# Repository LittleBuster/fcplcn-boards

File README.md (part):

# FCPLCn — платы контроллера

**Future City PLC Next · FCPLCN-161608-1v0**

**16 реле · 16 дискретных входов · 8 DATA-линий · Ethernet · Wi-Fi · RS-485 · iButton LED/звук**

Двухплатный PLC для локальной автоматики квартиры, частного дома и дачи.
Верхняя плата содержит процессор, сетевые интерфейсы, часы и полевые порты.
Нижняя — реле, входы, расширители GPIO, энергонезависимую FRAM и вход питания.
Прошивка выполняет местную логику управления, а Linux-хаб объединяет несколько PLC
в общий умный дом.

<p align="center">
  <a href="#overview">Характеристики</a> ·
  <a href="#cpu">CPU-плата</a> ·
  <a href="#relay">Реле и входы</a> ·
  <a href="#ports">Разъёмы и GPIO</a> ·
  <a href="#ibutton">iButton-панель</a> ·
  <a href="#power">Питание</a> ·
  <a href="#schematics">Схемы</a> ·
  <a href="#files">Файлы проекта</a>
</p>

Рендеры показывают конструкцию комплекта. Характеристики ниже сверены с текущими
схемами, нетлистами и BOM; токи обозначены как расчётные бюджеты.
Подробная аппаратная квалификация образца остаётся отдельным этапом.

Для тестового устройства предыдущего поколения **FCPLC-080806-3v1** также добавлены
[исправленная PDF-схема и сведения о подключении EEPROM](FCPLC-080806-3v1/README.md).
Его профиль в прошивке использует 8 реле, 8 входов и EEPROM 24LC512 вместо FRAM.

## Комплект FCPLCN-161608-1v0

| Узел              | Исполнение                                                               |
| ----------------- | ------------------------------------------------------------------------ |
| Верхняя плата     | **FCPLCN-CPU-08-1v0**, 90,5 × 49,44 мм                                     |
| Нижняя плата      | **FCPLCN-RLY-1616-1v0**, 101 × 86 мм                                     |
| Процессор         | ESP32-S3-WROOM-1U-N16R8, внешняя антенна 2,4 ГГц                         |
| Память процессора | 16 МиБ Flash и 8 МиБ PSRAM                                               |
| Релейные выходы   | 16 независимых нормально разомкнутых пар **COM/NO**                      |
| Дискретные входы  | 16 входов для сухого контакта с TLP2363 и RC-фильтрами                   |
| DATA              | 8 линий через ISO1640 для интерфейсов с открытым стоком                  |
| Сеть              | Wi-Fi ESP32-S3 и Ethernet на W5500-Lite / USR-ES1                        |
| RS-485            | ADM2687EBRIZ, полудуплекс, управление направлением через GPIO            |
| iButton-панель    | J9: LED− / BZ− через ULN2001 и общий защищённый +12V                    |
| Часы              | DS3231MZ+, резервирование от **CR1220 3 В**                              |
| FRAM              | FM24CL64B-GTR, **8192 байта**, на нижней плате                           |
| Питание комплекта | Внешние **12 В DC**, ввод на нижней плате                                |
| Технология PCB    | Обе платы двухслойные, толщина 1,6 мм                                    |
| Спецификация      | CPU **164** + RLY **248** = **412** покупных деталей; батарейка отдельно |

Числа `16 / 16 / 08` в обозначении комплекта соответствуют реле, дискретным входам
и DATA-линиям. Это одна аппаратная конфигурация с двумя физическими платами.

### Как связаны платы

Внутренняя I²C соединяет ESP32-S3, два MCP23017, FRAM и RTC. Отдельная линия
сбрасывает расширители GPIO. Межплатные разъёмы передают защищённые 12 В и GND; местные 5 В и 3,3 В между платами не передаются.
Внешние DATA, I²C и RS-485 отделены от основной логики барьером, но используют
**общую `GND_ISO`**. Дискретные входы относятся к основной GND.

## Верхняя плата — FCPLCN-CPU-08-1v0

CPU-плата отвечает за автономную логику PLC, подключение к локальной сети,
чтение полевых датчиков и сервисный USB. ESP32-S3 установлен в исполнении
с разъёмом внешней антенны. W5500 подключён по SPI; разъём RJ45 расположен
у переднего края сборки.

На обратной стороне находятся RTC, держатель батарейки и часть обвязки:

| Обозначение  | Компонент                | Назначение                                     |
| ------------ | ------------------------ | ---------------------------------------------- |
| U1           | ESP32-S3-WROOM-1U-N16R8  | Контроллер, Wi-Fi, Flash и PSRAM               |
| U2           | W5500-Lite / USR-ES1     | Проводной Ethernet по SPI                      |
| U3           | R-78K3.3-1.0             | Основное питание CPU 3,3 В                     |
| U4           | TMR-1-0511               | Изолированное питание 5 В, всего 1 Вт          |
| U5           | R-78K3.3-0.5             | Полевое питание `3V3_ISO`                      |
| U6/U8/U9/U15 | ISO1640BDR               | Восемь DATA-линий, по две на микросхему        |
| U7           | ISO1640BDR               | Внешняя I²C на J5                              |
| U10 / BT1    | DS3231MZ+ / Q&J CR1220-2 | Часы и резервная батарейка                     |
| U11          | ADM2687EBRIZ             | Изолированный трансивер RS-485                 |
| U12          | R-78K3.3-0.5             | Отдельное основное питание RS-485 3,3 В        |
| U13/U14      | Nexperia 74LVC125AD,118  | Буферы сигналов между основными цепями питания |
| U16          | ULN2001D1013TR          | Управляемые минусы LED и буззера iButton-панели |
| U17          | R-78E5.0-1.0            | Местные 5 В для входа TMR, от защищённых 12 В |

### DATA и внешняя I²C

J3 выводит восемь DATA-линий, питание `5V_ISO` и `GND_ISO`. Это линии
с открытым стоком: в аппаратном профиле они соответствуют `sens-0/1`…`sens-0/8`.
Они предусмотрены для трёхпроводных OneWire/DHT22-подключений с отдельным питанием.
Полевые подтяжки DATA подключены к **5 В**.

J5 — отдельная внешняя I²C: `3V3_ISO`, SDA, SCL, `GND_ISO`.
Её сигналы подтянуты к **3,3 В**. Она использует другую пару GPIO, чем внутренняя
шина расширителей и памяти. Устройства на J5 не занимают адреса внутренней I²C.

### RS-485

J8 содержит `5V_ISO`, A/D+, B/D− и `GND_ISO`. GPIO48 управляет направлением:
HIGH — передача, LOW — приём. Терминатор **120 Ом** включается перемычкой JP2,
расположенной спереди между J3 и J8 рядом с надписью `120R`.

Питание 5 В на J8 поступает от общего полевого TMR. Внутренний источник isoPower
ADM2687E обслуживает сам трансивер и не является источником питания DATA/I²C.
Конкретный протокол RS-485 задаётся программным обеспечением; наличие трансивера
не означает автоматическую поддержку любого протокола.

### Индикация и звук iButton-панели

**J9 — трёхконтактный KF128-2.54-3P** на нижнем переднем краю CPU-платы,
между Ethernet и DATA. Ввод проводов направлен наружу. На рендере сверху
контакты идут слева направо:

| Контакт J9 | Надпись на плате | Подключение панели | Управление |
| ---------- | ---------------- | ------------------ | ---------- |
| 1 | **LED−** | Катод светодиода | GPIO43, HIGH — включён |
| 2 | **BZ−** | Минус буззера | GPIO45, HIGH — включён |
| 3 | **+12V** | Анод LED и плюс буззера | Общая защищённая ветка питания |

Выходы LED− и BZ− замыкают нагрузку на основную GND через
**ULN2001D1013TR, SOIC-16, шаг 1,27 мм**. Драйвер U16 и основная обвязка
расположены на обратной стороне CPU-платы под W5500.

Для голого светодиода на плате предусмотрен R75 **1 кОм / 0,5 Вт, 0805**:
анод LED подключается к +12V, катод — к LED−. Ожидаемый ток около 6–8 мА.
Буззер подключается плюсом к +12V, минусом к BZ−; расчётная нагрузка —
до 100 мА. Для активного буззера достаточно ON/OFF, пассивный требует частотного
сигнала в прошивке. Точный тип и рабочее напряжение проверяются на реальном буззере.

Питание панели проходит через PTC, SS14 и местные 22 мкФ + 100 нФ;
SMAJ15A ограничивает выбросы, COM драйвера подключён к этой же ветке.
«12V» означает номинальную 12-вольтовую систему: при полной расчётной нагрузке
с учётом потерь на фильтре, диоде, PTC и ULN на буззере возможно около 8,5–9 В.

GPIO43 подтянут к основной GND через R73 10 кОм. R74 10 кОм подключён к базе
буззера; GPIO45 подтянут через R72 + R74, всего 10,68 кОм, когда вывод высокоимпедансный.
GPIO45 является загрузочным: LOW сохраняет 3,3 В VDD_SPI при штатных eFuse ESP32-S3.
GPIO43 может активно управляться ROM UART0 TX до настройки приложением; подтяжка
не подавляет этот сигнал, поэтому LED может мигать или гореть при загрузке.
Для постоянных логов предусмотрена USB-консоль.

**Сам сокет ключа iButton подключается отдельно к выбранной линии DATA на J3
и GND_ISO.** J9 обслуживает только свет и звук; отдельного GND на нём нет.
Контакты сокета не следует соединять с цепями LED/буззера и основной GND внутри панели.

### RTC и USB

DS3231MZ+ находится на внутренней I²C по адресу **`0x68`**. Батарейка —
**CR1220 3 В**, держатель Q&J CR1220-2, LCSC C70381; покупается отдельно.
FRAM имеет самостоятельное энергонезависимое хранение и батарейки не требует.

USB-C J2 используется для штатного USB Serial/JTAG ESP32-S3. D−/D+ подключены
к GPIO19/20, VBUS контролируется через GPIO21. **Для работы и прошивки через USB
нужно штатное питание 12 В:** USB VBUS служит сигналом контроля и не питает платы.
На плате доступны кнопки RESET и BOOT.

## Нижняя плата — FCPLCN-RLY-1616-1v0

Нижняя плата объединяет шестнадцать реле, шестнадцать дискретных входов,
два MCP23017, FRAM и питание всего комплекта. Верхний ряд клемм — выходные
контакты реле, нижний — входы DI с соседними GND; справа расположен ввод 12 В.

### Реле

K1…K16 — **HF49FD/012-1H11** с катушками 12 В. Каждый канал имеет свою пару
COM/NO на отдельном клеммнике J2…J17. Силовые COM разных каналов внутри платы
не объединены. U3/U4 **TBD62083AFWG** управляют катушками, а RN1/RN2 задают
подтяжки управляющих линий к GND.

```text
Реле выключено:  COM  o     o  NO
Реле включено:   COM  o─────o  NO

MCP23017 → TBD62083AFWG → катушка K1…K16
```

При сборке допустимая нагрузка определяется всем трактом: контактами выбранного
реле, дорожками, клеммами и проводкой. Число каналов не задаёт допустимый ток
силовой части.

### Дискретные входы

J21/J25/J29/J33 принимают четыре группы по четыре сухих контакта.
У каждого DI рядом расположен GND. Состояния на стороне MCP23017:

| Контакт между DI и GND | Уровень входа |
| ---------------------- | ------------- |
| Разомкнут              | **HIGH**      |
| Замкнут                | **LOW**       |

Каждый канал содержит TLP2363, входной TVS, обратный диод и две ступени фильтрации.
В текущей ревизии входная цепь использует **1,2 кОм**, последовательные **220 Ом**,
ёмкость **1 мкФ** и шунт LED **4,7 кОм**. На выходе остаются **470 Ом / 100 нФ**
и внешняя подтяжка RAW-сигнала **10 кОм**. Внутренние подтяжки MCP23017 отключены.

Цепь LED питается от внутренних 12 В. DI рассчитан на замыкание сухим контактом;
его нельзя трактовать как свободный GPIO 3,3 В. **Земля DI общая с логикой**:
TLP2363 здесь не образуют отдельный гальванически изолированный домен входов.
Примеры назначений — возвратная кнопка, геркон или релейный выход датчика.

### Расширители и FRAM

U5/U6 **MCP23017** обслуживают по восемь реле и восемь входов.
Обозначения портов MCP повторяются на каждой микросхеме:

| Номер в группе | Реле      | Дискретный вход |
| -------------- | --------- | --------------- |
| 1…7            | GPA1…GPA7 | GPB0…GPB6       |
| 8              | GPB7      | GPA0            |

U5 соответствует каналам **1…8**, U6 — **9…16**. Маска выходов — `0x80FE`,
входов — `0x7F01`. Аппаратный RESET расширителей приходит с CPU GPIO6;
INTA/INTB не подключены.

U9 **FM24CL64B-GTR** хранит 8192 байта без питания. A0/A1/A2 подключены к GND,
поэтому адрес — `0x50`; WP также на GND, запись разрешена. Память подключена
к той же внутренней шине, что расширители и RTC. В прошивке она используется
для сохранения оперативных состояний оборудования.

| Внутренняя I²C · GPIO4/5 | Адрес, 7 бит | Размещение                |
| ------------------------ | ------------ | ------------------------- |
| MCP23017 U5              | `0x20`       | Нижняя плата, каналы 1…8  |
| MCP23017 U6              | `0x21`       | Нижняя плата, каналы 9…16 |
| FRAM FM24CL64B-GTR U9    | `0x50`       | Нижняя плата              |
| RTC DS3231MZ+ U10        | `0x68`       | Верхняя плата             |

## Разъёмы и аппаратные имена

**Нумерация ниже — номера контактов в KiCad**, а не направление слева направо
на произвольно повёрнутом рендере. Первый контакт сверяется по исходнику и
маркировке конкретного разъёма.

| Плата / разъём | Назначение         | Контакты по номерам                                     |
| -------------- | ------------------ | ------------------------------------------------------- |
| RLY · J1       | Питание комплекта  | 1 — +12 В DC; 2 — GND                                   |
| RLY · J2…J17   | Реле 1…16          | 1 — COM; 2 — NO                                         |
| RLY · J21      | Входы 1…4          | Нечётные 1/3/5/7 — DI1/2/3/4; чётные — GND              |
| RLY · J25      | Входы 5…8          | Нечётные 1/3/5/7 — DI5/6/7/8; чётные — GND              |
| RLY · J29      | Входы 9…12         | Нечётные 1/3/5/7 — DI9/10/11/12; чётные — GND           |
| RLY · J33      | Входы 13…16        | Нечётные 1/3/5/7 — DI13/14/15/16; чётные — GND          |
| CPU · J3       | DATA, 10 контактов | 1…8 — DATA1…8; 9 — 5V_ISO; 10 — GND_ISO                 |
| CPU · J5       | Внешняя I²C        | 1 — 3V3_ISO; 2 — SDA_ISO; 3 — SCL_ISO; 4 — GND_ISO      |
| CPU · J8       | RS-485             | 1 — 5V_ISO; 2 — A/D+; 3 — B/D−; 4 — GND_ISO             |
| CPU · J9       | iButton LED / звук | 1 — LED−; 2 — BZ− (BUZZER−); 3 — +12V панели             |
| CPU · J7       | Передняя индикация | 1 — NET; 2 — PWR; 3 — STATUS; 4 — ALARM; 5 — GND        |
| CPU · J2       | Сервисный USB-C    | USB D−/D+, VBUS sense; внешнее питание 12 В сохраняется |

### Две штатные межплатные пары

Нижние гнёзда — Samtec **SSW-103-01-L-D**, верхние гребёнки —
**TSW-103-07-L-D**. У каждой пары шесть контактов, всего между платами их двенадцать.

| Контакт | Нижний J43 ↔ верхний J1 | Нижний J44 ↔ верхний J6 |
| ------- | ----------------------- | ----------------------- |
| 1       | GND                     | GND                     |
| 2       | GND                     | GND                     |
| 3       | GND                     | +12V_LOGIC              |
| 4       | GND                     | +12V_LOGIC              |
| 5       | I2C_SDA, GPIO4          | MCP_RESET_N, GPIO6      |
| 6       | I2C_SCL, GPIO5          | GND                     |

Обозначения J1 и J6 здесь относятся к CPU; RLY J1 — отдельный ввод питания.
В текущей CAD-ревизии дополнительных механических пар разъёмов нет.

### GPIO ESP32-S3

| Назначение                   | GPIO                             |
| ---------------------------- | -------------------------------- |
| Внутренняя I²C SDA / SCL     | **4 / 5**                        |
| RESET MCP23017               | **6**                            |
| W5500 CS / SCK / MOSI / MISO | **9 / 10 / 11 / 12**             |
| W5500 INT_N / RESET_N        | **13 / 14**                      |
| USB D− / D+ / VBUS sense     | **19 / 20 / 21**                 |
| RS-485 TX / RX / DIR         | **8 / 47 / 48**                  |
| Внешняя I²C SDA / SCL        | **41 / 42**                      |
| DATA1…DATA8                  | **39, 40, 17, 18, 1, 2, 38, 44** |
| NET / STATUS / ALARM         | **7 / 15 / 16**, активный LOW    |
| iButton LED / BUZZER         | **43 / 45**, HIGH включает нагрузку |
| BOOT                         | **0**                            |

PWR показывает основное питание 3,3 В. GPIO35–37 оставлены неподключёнными
для варианта N16R8 с Octal PSRAM. GPIO44 уже используется DATA8. GPIO43/45 заняты панелью; на них установлены внешние подтяжки к GND. GPIO3 оставлен NC.

В профиле прошивки каналы имеют имена `rly-0/1`…`rly-0/16`,
`in-0/1`…`in-0/16` и `sens-0/1`…`sens-0/8`.
[Профиль аппаратуры в fcplcn-soft](https://github.com/LittleBuster/fcplcn-soft/blob/main/firmware/base/main/hardware/board_profile.cpp).

## Питание и домены земли

[Открыть схему питания SVG](docs/readme/power-domains.svg).
Ниже **CPU** означает верхнюю плату, **RLY** — нижнюю; одинаковые номера
компонентов на разных платах обозначают разные детали.

### Ввод 12 В и ветка логики

Питание приходит на **RLY J1**: `+12V / GND`. Последовательные
**F1 Littelfuse 045201.5MRL, 1,5 А** и **D1 SS34** ведут к `+12V_SYS`.
D1 блокирует обратную полярность в этой ветке; **D2 SMBJ15A** подключён
между `+12V_SYS` и GND для ограничения кратковременных выбросов.
C1/C11/C12 образуют накопительный банк **300 мкФ / 35 В**.

От `+12V_SYS` питаются **катушки 16 реле** и **светодиодные входные цепи
TLP2363**. Сухие COM/NO контакты реле электрически отделены от катушек:
напряжение коммутируемой нагрузки подаётся на них извне.

Ветка электроники идёт отдельно:
`+12V_SYS → D3 B340B → +12V_LOGIC_RAW → R12 1 Ом → +12V_LOGIC`.
**C8 220 мкФ / 35 В** и **C13 100 нФ** подключены после R12.
D3 отделяет накопленную энергию этой ветки от катушек, а R12/C8/C13
образуют фильтр питания логики. Из-за падений на диодах и R12
`+12V_LOGIC` ниже напряжения внешнего блока питания.

### Четыре местных преобразователя

Все четыре получают `+12V_LOGIC` и работают относительно основной **GND**.
Модули **R-78 — импульсные стабилизаторы без гальванической изоляции**.

| Плата и источник | Выход и его потребители | Номинал модуля | Выделенный расчётный ток |
| --- | --- | --- | --- |
| **RLY U2, R-78K3.3-0.5** | `+3V3_DCDC → FB1 → +3V3`: MCP23017, FRAM, выходные стороны TLP2363 и их обвязка | **3,3 В / 500 мА** | **100 мА**; компонентная оценка **82,9 мА** |
| **CPU U3, R-78K3.3-1.0** | Основные `+3V3`: ESP32-S3, W5500, RTC, основные стороны ISO1640, индикация и обвязка | **3,3 В / 1 А** | **902 мА** |
| **CPU U12, R-78K3.3-0.5** | `+3V3_RS485`: основная сторона ADM2687E, локальный буфер и подтяжки | **3,3 В / 500 мА** | **201 мА** |
| **CPU U17, R-78E5.0-1.0** | Местные `+5V_TMR`: только вход изолированного TMR U4 | **5 В / 1 А** | **300 мА** |

Нижний **FB1 — Murata BLM21PG221SN1D**, ферритовый фильтр с малым
сопротивлением постоянному току. C3/C6 находятся до него, C7 и местные
100 нФ микросхем — после. Нижнего линейного стабилизатора U8 больше нет.
Обе платы имеют собственные 3,3 В; **их выходы между собой не соединены**.

Между платами питание передаётся только как **`+12V_LOGIC` и GND**:
справа J44/J6 контакты **3/4 — +12V_LOGIC**, **1/2/6 — GND**, **5 — RESET MCP**.
Слева J43/J1 контакты **1–4 — GND**, **5/6 — SDA/SCL**.
Местные 5 В и 3,3 В через межплатные разъёмы не проходят.

### Питание датчиков и полевой стороны

На CPU цепочка начинается с **U17**:
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
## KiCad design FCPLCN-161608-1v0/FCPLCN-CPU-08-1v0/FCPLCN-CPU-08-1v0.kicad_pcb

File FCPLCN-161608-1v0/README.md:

# FCPLCN-161608-1v0

**FCPLCn — Future City PLC Next.** Двухплатный комплект:
16 реле, 16 дискретных входов, 8 DATA-линий и выходы LED/буззера iButton-панели.

Подробное актуальное описание, питание, GPIO и распиновки:
**[основной README репозитория](../README.md)**.

## Платы и исходники

| Плата                      | Проект KiCad                                                | Принципиальная схема                                       | Читаемый PDF                                  |
| -------------------------- | ----------------------------------------------------------- | ---------------------------------------------------------- | --------------------------------------------- |
| Верхняя CPU, 90,5 × 49,44 мм | [Проект](FCPLCN-CPU-08-1v0/FCPLCN-CPU-08-1v0.kicad_pro)     | [KiCad](FCPLCN-CPU-08-1v0/FCPLCN-CPU-08-1v0.kicad_sch)     | [PDF](FCPLCN-CPU-08-1v0/FCPLCN-CPU-08-1v0-schematic.pdf)   |
| Нижняя RLY, 101 × 86 мм    | [Проект](FCPLCN-RLY-1616-1v0/FCPLCN-RLY-1616-1v0.kicad_pro) | [KiCad](FCPLCN-RLY-1616-1v0/FCPLCN-RLY-1616-1v0.kicad_sch) | [PDF](FCPLCN-RLY-1616-1v0/FCPLCN-RLY-1616-1v0-schematic.pdf) |

CPU содержит ESP32-S3-WROOM-1U-N16R8, W5500-Lite, RTC DS3231MZ+,
полевые DATA/I²C и трансивер RS-485 ADM2687E. На нижней плате расположены
реле HF49FD/012-1H11, входные TLP2363 с RC-фильтрами, два MCP23017
и FRAM FM24CL64B-GTR на 8192 байта.

Текущая комплектация: **CPU 164 + RLY 248 = 412** покупных деталей;
батарейка **CR1220 3 В** покупается отдельно. Обе платы двухслойные, 1,6 мм.
Две штатные пары межплатных разъёмов передают питание, I²C и RESET MCP.
Дополнительные механические пары удалены из текущих исходников.

## Питание двух плат

**12 В DC** подаются на нижний **J1**. После предохранителя **F1 1,5 А**
и диода **D1 SS34** получается `+12V_SYS`; **D2 SMBJ15A** ограничивает
кратковременные выбросы, C1/C11/C12 образуют банк 300 мкФ / 35 В.
Эта ветка питает катушки реле и светодиодные входные цепи TLP2363.
Сухие COM/NO контакты коммутируют внешнюю нагрузку, собственных 12 В на них нет.

Ветка электроники отделена фильтром:
`+12V_SYS → D3 B340B → R12 1 Ом → +12V_LOGIC`,
с C8 220 мкФ и C13 100 нФ после R12. Защищённые `+12V_LOGIC`
питают четыре местных импульсных преобразователя без гальванической изоляции:

| Плата и модуль | Питает | Номинал выхода | Выделено по расчёту |
| --- | --- | --- | --- |
| **RLY U2 R-78K3.3-0.5** | Через **FB1 BLM21PG221SN1D** — местные 3,3 В MCP23017, FRAM и выходных сторон TLP2363 | **3,3 В / 500 мА** | **100 мА**, компонентная оценка **82,9 мА** |
| **CPU U3 R-78K3.3-1.0** | ESP32-S3, W5500, RTC, основные стороны изоляторов и обвязка | **3,3 В / 1 А** | **902 мА** |
| **CPU U12 R-78K3.3-0.5** | Основная сторона ADM2687E, буфер и подтяжки | **3,3 В / 500 мА** | **201 мА** |
| **CPU U17 R-78E5.0-1.0** | Только вход TMR U4, местная `+5V_TMR` | **5 В / 1 А** | **300 мА** |

На RLY C3/C6 находятся до FB1, C7 и местные 100 нФ — после него;
нижний линейник U8 удалён. Питание между платами передаётся только как **12 В и GND**:
правый J44/J6 — питание и RESET, левый J43/J1 — I²C и GND.
Контакты 1–4 левой пары — GND. Шины **5 В и 3,3 В между платами не передаются**.

На CPU `+5V_TMR → U4 TMR-1-0511 → +5V_ISO / GND_ISO` —
изолированное питание поля **5 В / 200 мА, всего 1 Вт**.
Оно поступает на **J3.9 DATA**, **J8.1 RS-485** и полевые стороны DATA-изоляторов.
От этой же шины **U5 R-78K3.3-0.5** формирует `+3V3_ISO` для **J5.1 I²C**
и полевой стороны её изолятора. U5 имеет номинал 500 мА, но доступная мощность
ограничена общим TMR. На собственную полевую электронику выделено 55 мА
в эквиваленте 5 В, на все внешние устройства — **120 мА суммарно**;
общий бюджет поля — 175 из 200 мА. Это общий лимит DATA/I²C/RS-485,
а не отдельный лимит каждого разъёма.

Встроенный **isoPower ADM2687E** отдельно питает только шинную сторону
самого трансивера: `VISOOUT10 → CPU FB1 → VISOIN15`.
Он не соединён с `+3V3_ISO`; питание на J8 приходит от TMR.
DATA, внешняя I²C и шинная сторона RS-485 имеют общую **GND_ISO**,
без изоляции портов друг от друга. Основная **GND** объединяет CPU и RLY.

LED/буззер панели питаются от `+12V_LOGIC` через **CPU F2 PTC и D11 SS14**
на `+12V_PANEL / J9`; ULN2001 управляет их минусами относительно основной GND.
Бюджет панели — **108 мА**. CR1220 резервирует только RTC; зарядной цепи нет.
**USB VBUS используется только для контроля на GPIO21** и не питает платы:
для работы и прошивки через USB нужны внешние **12 В**.

Все токи — расчётные бюджеты, не измеренные максимумы. Для входа TMR при 1 Вт
и типовом КПД 76% получается 263,158 мА; выделено 300 мА.
Модель всего комплекта даёт около **0,995–1,012 А от 12 В**.
Подробности и допущения — [основное описание питания](../README.md#power),
[бюджет](Power-budget.json) и [расчёт](Power-split-design-review.json).

## CPU сверху и подключение iButton-панели

Клеммник **J9, KF128-2.54-3P**, находится на нижнем переднем краю CPU-платы
между Ethernet и DATA. На виде сверху контакты идут слева направо:

| Контакт | Надпись | Подключение |
| ------- | ------- | ----------- |
| 1 | **LED−** | Катод LED; GPIO43 через ULN2001 |
| 2 | **BZ−** | Минус буззера; GPIO45 через ULN2001 |
| 3 | **+12V** | Общий плюс LED и буззера |

HIGH включает соответствующую нагрузку. Резистор LED **1 кОм / 0,5 Вт**
установлен на CPU-плате; ток LED около **6–8 мА**, расчётный ток буззера —
до **100 мА**. Это номинальная 12-вольтовая ветка: при полной расчётной
нагрузке напряжение на буззере может снизиться примерно до **8,5–9 В**.
При загрузке GPIO43 используется ROM UART0 TX, поэтому LED может мигать или гореть.

Сам сокет ключа подключается отдельно к выбранной **DATA на J3 и GND_ISO**.
J9 обслуживает свет и звук и не содержит отдельного GND. Контакты сокета
не соединяются с цепями LED/буззера и основной GND внутри панели.

## Нижняя RLY сверху и под наклоном

## Проверка изготовления CPU

[Текущий отчёт](Power-split-validation.json) связывает исходники с проверками соединений, производственных зазоров, изоляции, USB и механики. Параметры — [профиль завода](Power-split-profile.json). Локальные переходы с кольцом 0,15 мм и посадка DIP USB-C используют опубликованные предельные возможности производства; обычное кольцо — 0,20 мм. Для ручной сборки учтите [список отверстий под предварительное заполнение припоем](Power-split-via-prefill-CPU.csv) и [заметки сборки](ASSEMBLY.md).

## Документация и материалы

- [Общий BOM](BOM-combined.csv).
- Схемы PDF: [CPU](FCPLCN-CPU-08-1v0/FCPLCN-CPU-08-1v0-schematic.pdf), [RLY](FCPLCN-RLY-1616-1v0/FCPLCN-RLY-1616-1v0-schematic.pdf). Схемы SVG/PNG находятся в каталогах соответствующих плат.
- [Галерея ракурсов](Previews/native-all-views/index.html) — открыть локально после скачивания.
- [Архив KiCad](FCPLCN-161608-1v0-KiCad.zip).
- [Архив 3D-видов](FCPLCN-161608-1v0-3D-views.zip).
- [Заметки сборки и предшествующие изменения](ASSEMBLY.md).
- [Текущий бюджет питания](Power-budget.json).
- [Геометрия сборки](Stack-mechanics.json).
- [Актуальный отчёт с контрольными суммами](Power-split-validation.json).
- [Инструменты аппаратных проверок](tools/README.md).
- [История аппаратных операций](CHANGELOG.md).

Локальные библиотеки, посадочные места и 3D-модели следует сохранять рядом
с платами: пути используют `${KIPRJMOD}`. Стандартные библиотеки KiCad 10
устанавливаются отдельно. `Manufacturing-validation.json` описывает предыдущую CPU-ревизию с SHA `5ba899b9…`;
текущую ревизию подтверждает `Power-split-validation.json`. Старые отчёты подтверждают только собственные
контрольные суммы; актуальные номиналы и количество деталей приведены
в основном README, BOM и текущих исходниках.

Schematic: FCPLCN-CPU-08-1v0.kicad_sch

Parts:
BT1: CR1220-2; BatteryHolder_QJ_CR1220-2_C70381; MPN CR1220-2
C1: 10uF; C_1206_3216Metric; Voltage 35 V; Tolerance 10%; MPN C3216X7R1V106K160AC
C3, C4, C36, C37: 22uF 35V X5R; C_1206_3216Metric; Tolerance 20%; MPN C3216X5R1V226M160AC
C5, C8, C11, C12, C13, C38, C41, C54: 10uF; C_1206_3216Metric; Tolerance 10%; Voltage 35 V; MPN C3216X7R1V106K160AC
C6, C9, C14, C16, C18, C20, C22, C24, C26, C28, C39, C40, C42, C43, C46, C47, C48, C55, C56: 100nF; C_0805_2012Metric; Tolerance 10%; Voltage 50 V
C7: 1uF; C_0805_2012Metric
C10, C44, C45: 10nF; C_0805_2012Metric; Tolerance 10%; Voltage 50 V
C15, C17, C19, C21, C23, C25, C27, C29, C35, C49, C51: 1nF C0G; C_0805_2012Metric; Tolerance 5%; Voltage 50 V
C33, C53: 100nF; C_0805_2012Metric; Voltage 50 V; Tolerance 10%
C34: 100nF; C_1206_3216Metric
C50: 100nF; C0805_C50_Clearance; Tolerance 10%; Voltage 50 V
C52: 22uF / 35V; C_1206_3216Metric; Voltage 35 V; Tolerance 20%; MPN C3216X5R1V226M160AC
D1: SRDA05-4BTG; SOIC8_SRDA_USB_Clearance; MPN SRDA05-4BTG
D2, D3, D4, D6: SRDA05-4BTG; SOIC-8_3.9x4.9mm_P1.27mm; MPN SRDA05-4BTG
D9: SM712; SOT-23; MPN CDSOT23-SM712
D11: SS14; D_SMA; MPN SS14-E3/61T
D12: SMAJ15A; D_SMA; MPN SMAJ15A
F2: PTC 0.2A / 30V; Fuse_1206_3216Metric; MPN MF-NSMF020X-2
FB1: 220R @100MHz / 2A; L_0805_2012Metric; MPN BLM21PG221SN1D
J1: LEFT · GND / I2C; StackHeader_2x03_P2.54mm_Bottom
J2: HBXINTAO 16PIN DIP; USB_C_Receptacle_HBXINTAO16PIN_DIP_Vertical; MPN 16PIN
J3: DATA1–8 / 5V / GND; KF128-2.54-10P
J5: I²C; KF128-2.54-4P
J6: RIGHT · 12V / CTRL; StackHeader_2x03_P2.54mm_Bottom
J7: NET / PWR / STATUS / ALARM / GND; PinHeader_1x05_P2.54mm_Vertical
J8: RS-485 / 5V A B G; KF128-2.54-4P
J9: iButton LED / BUZZER / +12V; KF128-2.54-3P; MPN KF128-2.54-3P
JP2: TERM / normally open; PinHeader_1x02_P2.54mm_Vertical
Q1, Q2, Q3: BC807-40; SOT-23
R1, R2, R51, R52, R73, R74: 10k; R_0805_2012Metric; Tolerance 1%
R3: 1k; R_0805_2012Metric
R4, R23, R24, R25, R26, R46: 470R; R_0805_2012Metric; Tolerance 1%
R5, R6, R7, R8, R11, R12, R47, R48, R49: 22R; R_0805_2012Metric; Tolerance 1%
R9, R10: 5.1k; R_0805_2012Metric
R13: 68k; R_0805_2012Metric
R14, R30, R31, R32: 100k; R_0805_2012Metric
R15, R16, R19, R20, R33, R34, R37, R38, R57, R58: 4.3k; R_0805_2012Metric; Tolerance 1%
R17, R18, R21, R22, R27, R28, R29, R35, R36, R39, R40, R59, R60: 4.7k; R_0805_2012Metric; Tolerance 1%
R50, R54, R55, R56: 47k; R_0805_2012Metric; Tolerance 1%
R53: 120R 0.25W; R_1206_3216Metric; Tolerance 1%
R61, R62, R63, R64, R65, R66, R67, R68, R69, R70: 100R; R_0805_2012Metric; Tolerance 1%; MPN CRCW0805100RFKTAHP
R71, R72: 680R; R_0805_2012Metric; Tolerance 1%
R75: 1k / 0.5W; R_0805_2012Metric; Tolerance 1%; MPN ERJ-P06F1001V
SW1: RESET; SW_SPST_TS-1088-xR020
SW2: BOOT; SW_SPST_TS-1088-xR020
U1: ESP32-S3-WROOM-1U; ESP32-S3-WROOM-1U_PTH030; MPN ESP32-S3-WROOM-1U-N16R8
U2: W5500-Lite; W5500_Lite_2x6
U3: R-78K3.3-1.0; RECOM_R-78K3.3-1.0_SIP3_P2.54mm; MPN R-78K3.3-1.0
U4: TMR-1-0511; TMR1_SIP6
U5, U12: R-78K3.3-0.5; RECOM_R-78K3.3-0.5_SIP3_P2.54mm; MPN R-78K3.3-0.5
U6, U7, U8, U9, U15: ISO1640BDR; SOIC-8_3.9x4.9mm_P1.27mm; MPN ISO1640BDR
U10: DS3231MZ+; SOIC-8_3.9x4.9mm_P1.27mm; MPN DS3231MZ+
U11: ADM2687E; ADM2687E_SOIC_IC_16_7.5x12.75mm_P1.27mm; MPN ADM2687EBRIZ
U13, U14: 74LVC125AD,118; SOIC-14_3.9x8.7mm_P1.27mm; MPN 74LVC125AD,118
U16: ULN2001D1013TR; SOIC-16_3.9x9.9mm_P1.27mm; MPN ULN2001D1013TR
U17: R-78E5.0-1.0; RECOM_R-78E_PSE; MPN R-78E5.0-1.0

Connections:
/+3V3: C3.1, C4.1, C5.1, C6.1, C8.1, C9.1, C14.1, C15.1, C18.1, C19.1, C22.1, C23.1, C26.1, C27.1, C47.1, C48.1, C49.1, Q1.2 (E), Q2.2 (E), Q3.2 (E), R1.1, R2.1, R15.1, R16.1, R19.1, R20.1, R24.1, R30.2, R31.2, R32.2, R33.1, R34.1, R37.1, R38.1, R46.1, R50.1, R52.2, R57.1, R58.1, U1.2 (3V3), U2.2.2 (3V3), U2.2.3 (3V3), U3.3 (VOUT), U6.1 (VCC1), U7.1 (VCC1), U8.1 (VCC1), U9.1 (VCC1), U14.4 (2OE_N), U14.10 (3OE_N), U14.13 (4OE_N), U14.14 (VCC), U15.1 (VCC1)
/+3V3_ISO: C13.1, C20.1, C21.1, J5.1 (3V3), R21.1, R22.1, U5.3 (VOUT), U7.8 (VCC2)
/+3V3_RS485: C38.1, C39.1, C40.1, C45.1, C46.1, R54.1, R56.1, U11.2 (VCC), U11.7 (VCC), U12.3 (VOUT), U13.1 (1OE_N), U13.14 (VCC)
/+5V_ISO: C12.1, C16.1, C17.1, C24.1, C25.1, C28.1, C29.1, C50.1, C51.1, J3.9 (5V), J8.1 (5V_ISO), R17.1, R18.1, R35.1, R36.1, R39.1, R40.1, R59.1, R60.1, U4.4 (+VOUT), U5.1 (VIN), U6.8 (VCC2), U8.8 (VCC2), U9.8 (VCC2), U15.8 (VCC2)
/+5V_TMR: C11.1, C56.1, U4.2 (+VIN), U17.3 (VOUT)
/+12V_LOGIC: C1.1, C33.1, C37.1, C54.1, C55.1, F2.1, J6.3 (VIN), J6.4 (VIN), U3.1 (VIN), U12.1 (VIN), U17.1 (VIN)
/+12V_PANEL: C52.1, C53.1, D11.1 (K), D12.1 (K), J9.3 (+12V), U16.9 (COM)
/ALARM_LED: R29.1, U1.9 (IO16)
/DATA1_CPU: R15.2, U1.32 (IO39), U6.2 (SDA1)
/DATA1_IC_ISO: R17.2, R61.2, U6.7 (SDA2)
/DATA1_ISO: D2.1 (IO1), J3.1 (DATA1), R61.1
/DATA2_CPU: R16.2, U1.33 (IO40), U6.3 (SCL1)
/DATA2_IC_ISO: R18.2, R62.2, U6.6 (SCL2)
/DATA2_ISO: D2.4 (IO2), J3.2 (DATA2), R62.1
/DATA3_CPU: R33.2, U1.10 (IO17), U8.2 (SDA1)
/DATA3_IC_ISO: R35.2, R63.2, U8.7 (SDA2)
/DATA3_ISO: D2.6 (IO3), J3.3 (DATA3), R63.1
/DATA4_CPU: R34.2, U1.11 (IO18), U8.3 (SCL1)
/DATA4_IC_ISO: R36.2, R64.2, U8.6 (SCL2)
/DATA4_ISO: D2.7 (IO4), J3.4 (DATA4), R64.1
/DATA5_CPU: R37.2, U1.39 (IO1), U9.2 (SDA1)
/DATA5_IC_ISO: R39.2, R65.2, U9.7 (SDA2)
/DATA5_ISO: D6.1 (IO1), J3.5 (DATA5), R65.1
/DATA6_CPU: R38.2, U1.38 (IO2), U9.3 (SCL1)
/DATA6_IC_ISO: R40.2, R66.2, U9.6 (SCL2)
/DATA6_ISO: D6.4 (IO2), J3.6 (DATA6), R66.1
/DATA7_CPU: R57.2, U1.31 (IO38), U15.2 (SDA1)
/DATA7_IC_ISO: R59.2, R67.2, U15.7 (SDA2)
/DATA7_ISO: D6.6 (IO3), J3.7 (DATA7), R67.1
/DATA8_CPU: R58.2, U1.36 (RXD0), U15.3 (SCL1)
/DATA8_IC_ISO: R60.2, R68.2, U15.6 (SCL2)
/DATA8_ISO: D6.7 (IO4), J3.8 (DATA8), R68.1
/ESP_BOOT: R2.2, SW2.1, U1.27 (IO0)
/ESP_EN: C7.1, R1.2, SW1.1, U1.3 (EN)
/ETH_CS_CPU: R5.1, U1.17 (IO9)
/ETH_CS_N: R5.2, U2.1.5 (CS_N)
/ETH_INT_N: U1.21 (IO13), U2.1.6 (INT_N)
/ETH_MISO: R8.1, U2.2.6 (MISO)
/ETH_MISO_CPU: R8.2, U1.20 (IO12)
/ETH_MOSI: R7.2, U2.1.3 (MOSI)
/ETH_MOSI_CPU: R7.1, U1.19 (IO11)
/ETH_RST_F: C10.1, R4.2, U2.2.5 (RST_N)
/ETH_RST_N: R3.1, R4.1, U1.22 (IO14)
/ETH_SCK: R6.2, U2.1.4 (SCK)
/ETH_SCK_CPU: R6.1, U1.18 (IO10)
/GND: BT1.2 (−), C1.2, C3.2, C4.2, C5.2, C6.2, C7.2, C8.2, C9.2, C10.2, C11.2, C14.2, C15.2, C18.2, C19.2, C22.2, C23.2, C26.2, C27.2, C33.2, C34.2, C35.2, C36.2, C37.2, C38.2, C39.2, C40.2, C45.2, C46.2, C47.2, C48.2, C49.2, C52.2, C53.2, C54.2, C55.2, C56.2, D1.1 (IO1), D1.4 (IO2), D1.5 (REF2), D1.8 (REF2), D4.5 (REF2), D4.8 (REF2), D12.2 (A), J1.1 (GND), J1.2 (GND), J1.3 (VIN), J1.4 (VIN), J2.A1 (GND), J2.A12 (GND), J2.B1 (GND), J2.B12 (GND), J2.SH (Shield), J6.1 (GND), J6.2 (GND), J6.6 (SIG B), J7.5 (GND), R3.2, R9.2, R10.2, R14.2, R51.2, R55.2, R73.2, R74.2, SW1.2, SW2.2, U1.1 (GND), U1.40 (GND), U1.41 (EPAD), U2.1.1 (GND), U2.1.2 (GND), U2.2.1 (GND), U3.2 (GND), U4.1 (−VIN), U6.4 (GND1), U7.4 (GND1), U8.4 (GND1), U9.4 (GND1), U10.5 (GND), U11.1 (GND1), U11.8 (GND1), U12.2 (GND), U13.2 (1A), U13.4 (2OE_N), U13.5 (2A), U13.7 (GND), U13.10 (3OE_N), U13.13 (4OE_N), U14.1 (1OE_N), U14.5 (2A), U14.7 (GND), U14.9 (3A), U14.12 (4A), U15.4 (GND1), U16.1 (IN1), U16.2 (IN2), U16.3 (IN3), U16.4 (IN4), U16.5 (IN5), U16.8 (GND), U17.2 (GND)
/GND_ISO: C12.2, C13.2, C16.2, C17.2, C20.2, C21.2, C24.2, C25.2, C28.2, C29.2, C41.2, C42.2, C43.2, C44.2, C50.2, C51.2, D2.5 (REF2), D2.8 (REF2), D3.5 (REF2), D3.6 (IO3), D3.7 (IO4), D3.8 (REF2), D6.5 (REF2), D6.8 (REF2), D9.3 (GND), J3.10 (GND), J5.4 (GND), J8.4 (GND_ISO), U4.6 (−VOUT), U5.2 (GND), U6.5 (GND2), U7.5 (GND2), U8.5 (GND2), U9.5 (GND2), U11.9 (GND2), U11.16 (GND2), U15.5 (GND2)
/I2C_SCL: J1.6 (SIG B), U1.5 (IO5), U10.8 (SCL)
/I2C_SDA: J1.5 (SIG A), U1.4 (IO4), U10.7 (SDA)
/IB_12V_FUSED: D11.2 (A), F2.2
/IB_BUZZ_BASE: R72.2, R74.1, U16.6 (IN6)
/IB_BUZZ_CPU: R72.1, U1.26 (IO45)
/IB_BUZZ_OUT: J9.2 (BUZZER-), U16.11 (OUT6)
/IB_LED_BASE: R71.2, U16.7 (IN7)
/IB_LED_CPU: R71.1, R73.1, U1.37 (TXD0)
/IB_LED_OUT: J9.1 (LED-), R75.1
/IB_LED_SINK: R75.2, U16.10 (OUT7)
/ISO_SCL_CPU: R20.2, U1.35 (IO42), U7.3 (SCL1)
/ISO_SDA_CPU: R19.2, U1.34 (IO41), U7.2 (SDA1)
/LED_ALARM_BASE: Q3.1 (B), R29.2, R32.1
/LED_ALARM_DRIVE: Q3.3 (C), R26.1
/LED_ALARM_OUT: D4.6 (IO3), J7.4 (ALARM), R26.2
/LED_NET_BASE: Q1.1 (B), R27.2, R30.1
/LED_NET_DRIVE: Q1.3 (C), R23.1
/LED_NET_OUT: D4.1 (IO1), J7.1 (NET), R23.2
/LED_PWR_OUT: D4.7 (IO4), J7.2 (PWR), R24.2
/LED_STATUS_BASE: Q2.1 (B), R28.2, R31.1
/LED_STATUS_DRIVE: Q2.3 (C), R25.1
/LED_STATUS_OUT: D4.4 (IO2), J7.3 (STATUS), R25.2
/MCP_RESET_N: J6.5 (SIG A), U1.6 (IO6)
/NET_LED: R27.1, U1.7 (IO7)
/RS485_A: D9.1 (A), J8.2 (A / D+), R53.1, U11.11 (Y), U11.14 (A)
/RS485_B: D9.2 (B), J8.3 (B / D-), JP2.2, U11.12 (Z), U11.13 (B)
/RS485_DIR: R48.2, R55.1, U11.4 (RE_N), U11.5 (DE)
/RS485_DIR_BUF: R48.1, U13.8 (3Y)
/RS485_DIR_CPU: R51.1, U1.25 (IO48), U13.9 (3A)
/RS485_RX_BUF: R49.1, U14.3 (1Y)
/RS485_RX_CPU: R49.2, R52.1, U1.24 (IO47)
/RS485_RX_RAW: R56.2, U11.3 (RxD), U14.2 (1A)
/RS485_TERM: JP2.1, R53.2
/RS485_TX: R47.2, R54.2, U11.6 (TxD)
/RS485_TX_BUF: R47.1, U13.11 (4Y)
/RS485_TX_CPU: R50.2, U1.12 (IO8), U13.12 (4A)
/RS485_VISO: C43.1, C44.1, FB1.2, U11.15 (VISOIN)
/RS485_VISO_OUT: C41.1, C42.1, FB1.1, U11.10 (VISOOUT)
/RTC_VBAT: BT1.1 (+), C35.1, U10.6 (VBAT)
/RTC_VCC: C34.1, C36.1, R46.2, U10.2 (VCC)
/SCL_IC_ISO: R22.2, R70.2, U7.6 (SCL2)
/SCL_ISO: D3.4 (IO2), J5.3 (SCL), R70.1
/SDA_IC_ISO: R21.2, R69.2, U7.7 (SDA2)
/SDA_ISO: D3.1 (IO1), J5.2 (SDA), R69.1
/STATUS_LED: R28.1, U1.8 (IO15)
/TVS_DATA14_REF_ISO: D2.2 (REF1), D2.3 (REF1)
/TVS_DATA58_REF_ISO: D6.2 (REF1), D6.3 (REF1)
/TVS_I2C_REF_ISO: D3.2 (REF1), D3.3 (REF1)
/TVS_LED_REF: D4.2 (REF1), D4.3 (REF1)
/TVS_USB_REF: D1.2 (REF1), D1.3 (REF1)
/USB_CC1: J2.A5 (CC1), R9.1
/USB_CC2: J2.B5 (CC2), R10.1
/USB_DN: D1.6 (IO3), J2.A7 (DN1), J2.B7 (DN2), R11.1
/USB_DN_CPU: R11.2, U1.13 (IO19)
/USB_DP: D1.7 (IO4), J2.A6 (DP1), J2.B6 (DP2), R12.1
/USB_DP_CPU: R12.2, U1.14 (IO20)
/USB_VBUS: J2.A4 (VBUS), J2.A9 (VBUS), J2.B4 (VBUS), J2.B9 (VBUS), R13.1
/USB_VBUS_SENSE: R13.2, R14.1, U1.23 (IO21)

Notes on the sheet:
ESP32-S3 · external 2.4 GHz antenna
Native USB serial/JTAG · no external JTAG on GPIO39–42
W5500 Lite · RJ45 toward DI terminals
Assert reset for ≥1 ms. Wait ≥2 ms before SPI.
USB-C · all through-hole · service / programming
Power from base board. USB VBUS used only for sensing.
Local TMR supply · protected 12 V to 5 V / 1 A
C11 is the local 5 V bulk bypass at TMR input U4.
Left stack pins 1–4 are GND; 5 V and 3.3 V stay local.
Main power · protected 12 V to 3.3 V / 1 A
Independent 12 V main and RS-485 branches; 5 V feeds TMR.
Keep input / output decoupling close to the R-78K module.
Budget: main 3.3 V 902 mA; module output rated 1 A.
Main board interface · reset and boot
Base board powers MCP23017 and provides the I²C pull-ups.
Sensor power · isolated 5 V and 3.3 V
Keep the isolated ground separate across the stack.
DATA1/2 isolation · shared 10-pin terminal
Isolated I²C · 3.3 V field bus
Use 3-wire, externally powered sensors and open-drain GPIO.
TVS on connector side; 100R then isolator + 4.7k pull-up.
The field bus and base-board I²C use separate GPIO pairs.
Additional isolated DATA ports · GPIO17 / GPIO18
Additional isolated DATA ports · GPIO1 / GPIO2
DATA7/8 isolation · GPIO38 / GPIO44
GPIO44 is DATA8; keep UART0 RX disabled.
SRDA REF1 pins 2/3: local floating node; never connect to supply.
REF2 pins 5/8: local GND. FIELD TVS uses GND_ISO only.
Front-panel indicators
PWR follows 3.3 V. Other LEDs are active LOW at GPIO7 / 15 / 16.
LED anodes use NET / PWR / STATUS / ALARM, all cathodes use GND.
Battery-backed RTC · DS3231MZ+ / CR1220
0x68; main I²C. CR1220 primary cell; no charger.
RS-485 · ADM2687E · UART1 / GPIO8 TX, GPIO47 RX, GPIO48 DIR
ADM2687E pin10 VISOOUT feeds pin15 VISOIN only; never parallel with sensor 3V3_ISO.
GND2 shares GND_ISO. Terminal 5V comes from TMR. Fit TERM only at a bus end.
Nexperia Ioff buffers prevent backfeed between independent 3.3V rails. DIR defaults LOW.
iButton panel: bare LED and 12 V buzzer / two direct CPU GPIO
GPIO43 LED / GPIO45 BUZZER: HIGH = ON. GPIO43 is ROM UART TX; firmware must configure it as GPIO. GPIO45 reset pull-down: R72+R74=10.68k.
Bare LED: anode +12V_PANEL, cathode LED-. Buzzer: +12V_PANEL / BUZZER-. Design buzzer load <=100mA.

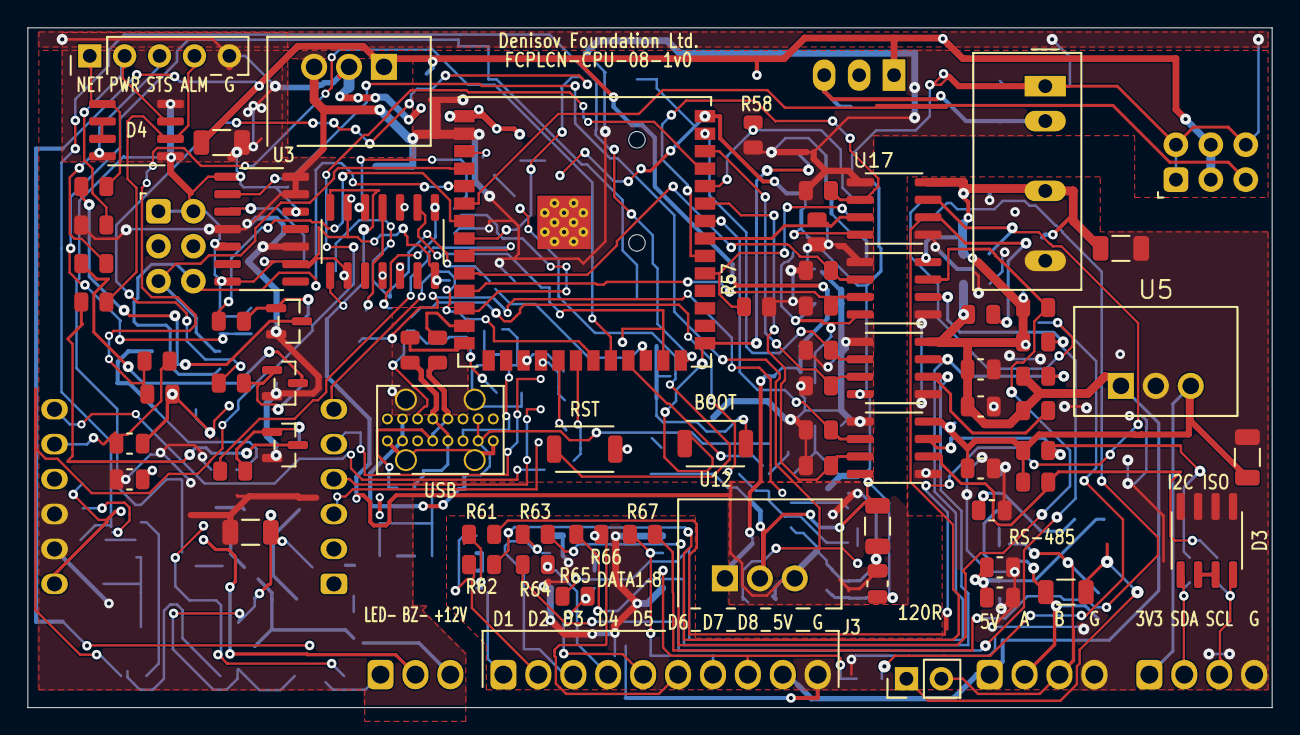
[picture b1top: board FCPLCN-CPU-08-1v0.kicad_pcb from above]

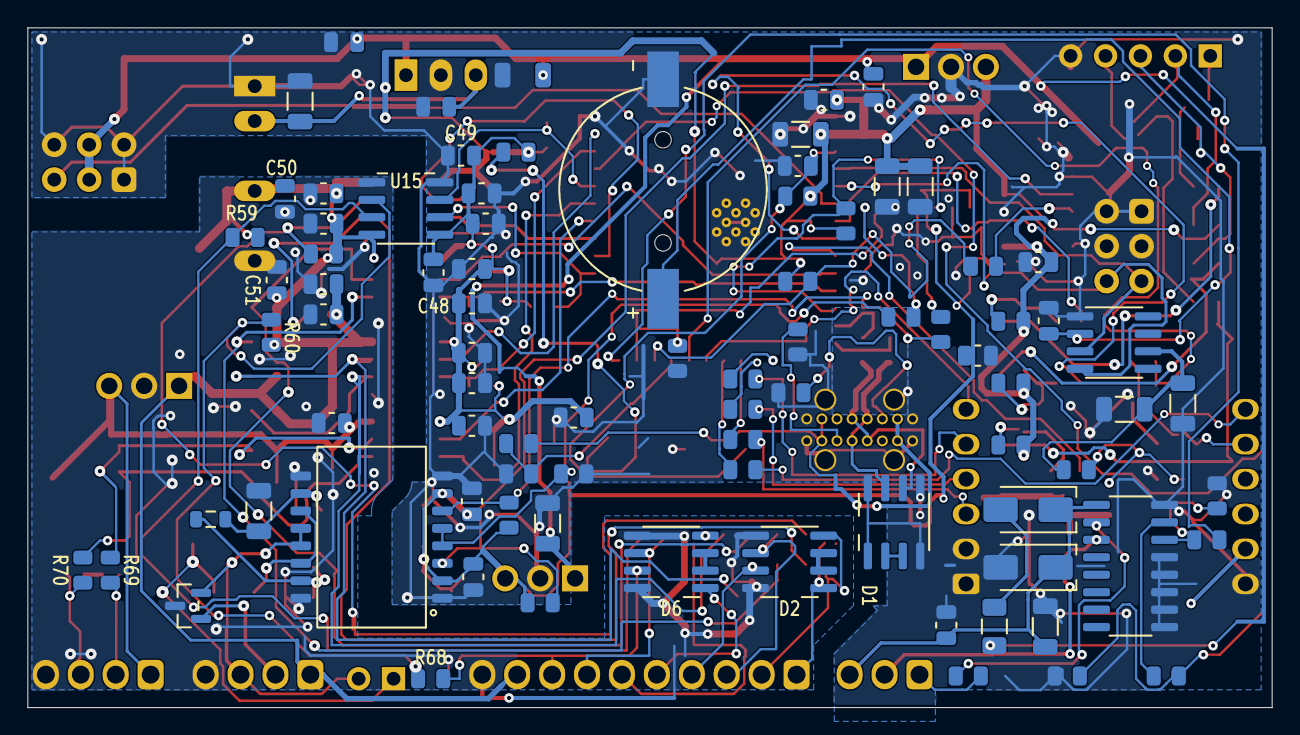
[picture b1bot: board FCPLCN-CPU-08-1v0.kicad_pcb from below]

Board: 2 copper layers, 90.5 x 49.4 mm, 164 parts (85 on the bottom side), 105 nets.

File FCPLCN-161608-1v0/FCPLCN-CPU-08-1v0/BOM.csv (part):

refs,value,footprint,qty,datasheet,mpn,manufacturer,tolerance,supplier_part_number,source_url,package,bom_group,power_rating,voltage,dielectric,resistor_type,height_max,cad_footprints
BT1,CR1220-2,RelayStack:BatteryHolder_QJ_CR1220-2_C70381,1,https://atta.szlcsc.com/upload/public/pdf/source/20240508/10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,CR1220-2,Q&J,,C70381,https://jlcpcb.com/partdetail/QJ-CR12202/C70381,RelayStack:BatteryHolder_QJ_CR1220-2_C70381,,,,,,,RelayStack:BatteryHolder_QJ_CR1220-2_C70381
"C1, C5, C8, C11, C12, C13, C38, C41, C54",10uF,Capacitor_SMD:C_1206_3216Metric,9,https://product.tdk.com/system/files/dam/doc/product/capacit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,C3216X7R1V106K160AC,TDK,10%,,,1206,C-1206-10uF-35V-X7R-10pct-TDK,,35 V,X7R,,1.8 mm,Capacitor_SMD:C_1206_3216Metric
"C3, C4, C36, C37",22uF 35V X5R,Capacitor_SMD:C_1206_3216Metric,4,https://product.tdk.com/en/system/files/dam/doc/product/capa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,C3216X5R1V226M160AC,TDK,20%,,,Capacitor_SMD:C_1206_3216Metric,,,,,,,Capacitor_SMD:C_1206_3216Metric
"C6, C9, C14, C16, C18, C20, C22, C24, C26, C28, C33, C39, C40, C42, C43, C46, C47, C48, C50, C53, C55, C56",100nF,Capacitor_SMD:C_0805_2012Metric; RelayStack:C0805_C50_Clearance,22,,,,10%,,,0805,C-0805-100nF-50V-X7R-10pct,,50 V,X7R,,,Capacitor_SMD:C_0805_2012Metric; RelayStack:C0805_C50_Clearance
C7,1uF,Capacitor_SMD:C_0805_2012Metric,1,,,,,,,Capacitor_SMD:C_0805_2012Metric,,,,,,,Capacitor_SMD:C_0805_2012Metric
"C10, C44, C45",10nF,Capacitor_SMD:C_0805_2012Metric,3,,,,10%,,,0805,C-0805-10nF-50V-X7R-10pct,,50 V,X7R,,,Capacitor_SMD:C_0805_2012Metric
"C15, C17, C19, C21, C23, C25, C27, C29, C35, C49, C51",1nF C0G,Capacitor_SMD:C_0805_2012Metric,11,,,,5%,,,0805,C-0805-1nF-50V-C0G-5pct,,50 V,C0G,,,Capacitor_SMD:C_0805_2012Metric
C34,100nF,Capacitor_SMD:C_1206_3216Metric,1,,,,,,,Capacitor_SMD:C_1206_3216Metric,,,,,,,Capacitor_SMD:C_1206_3216Metric
C52,22uF / 35V,Capacitor_SMD:C_1206_3216Metric,1,,C3216X5R1V226M160AC,TDK,20%,,,Capacitor_SMD:C_1206_3216Metric,,,35 V,X5R,,,Capacitor_SMD:C_1206_3216Metric
D1,SRDA05-4BTG,RelayStack:SOIC8_SRDA_USB_Clearance,1,https://www.littelfuse.com/assetdocs/tvs-diode-array-spa-srd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,SRDA05-4BTG,Littelfuse,,,,RelayStack:SOIC8_SRDA_USB_Clearance,,,,,,,RelayStack:SOIC8_SRDA_USB_Clearance
"D2, D3, D4, D6",SRDA05-4BTG,Package_SO:SOIC-8_3.9x4.9mm_P1.27mm,4,https://www.littelfuse.com/assetdocs/tvs-diode-array-spa-srd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,SRDA05-4BTG,Littelfuse,,,,Package_SO:SOIC-8_3.9x4.9mm_P1.27mm,,,,,,,Package_SO:SOIC-8_3.9x4.9mm_P1.27mm
D9,SM712,Package_TO_SOT_SMD:SOT-23,1,https://www.bourns.com/docs/product-datasheets/cdsot23-sm712.pdf,CDSOT23-SM712,Bourns,,,,Package_TO_SOT_SMD:SOT-23,,,,,,,Package_TO_SOT_SMD:SOT-23
D11,SS14,Diode_SMD:D_SMA,1,https://www.vishay.com/docs/88746/ss12.pdf,SS14-E3/61T,Vishay,,,,Diode_SMD:D_SMA,,,,,,,Diode_SMD:D_SMA
D12,SMAJ15A,Diode_SMD:D_SMA,1,https://www.littelfuse.com/assetdocs/tvs-diodes-smaj-datashe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,SMAJ15A,Littelfuse,,,,Diode_SMD:D_SMA,,,,,,,Diode_SMD:D_SMA
F2,PTC 0.2A / 30V,Fuse:Fuse_1206_3216Metric,1,https://www.bourns.com/docs/product-datasheets/mf-nsmf.pdf,MF-NSMF020X-2,Bourns,,,,Fuse:Fuse_1206_3216Metric,,,,,,,Fuse:Fuse_1206_3216Metric
FB1,220R @100MHz / 2A,Inductor_SMD:L_0805_2012Metric,1,https://www.murata.com/en-eu/api/pdfdownloadapi?cate=cgsubCh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,BLM21PG221SN1D,Murata,,,,Inductor_SMD:L_0805_2012Metric,,,,,,,Inductor_SMD:L_0805_2012Metric
J1,LEFT · GND / I2C,RelayStack:StackHeader_2x03_P2.54mm_Bottom,1,,,,,,,RelayStack:StackHeader_2x03_P2.54mm_Bottom,,,,,,,RelayStack:StackHeader_2x03_P2.54mm_Bottom
J2,HBXINTAO 16PIN DIP,RelayStack:USB_C_Receptacle_HBXINTAO16PIN_DIP_Vertical,1,https://connectorscn.com/wp-content/uploads/2026/10/b16-deta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,16PIN,HBXINTAO,,1005004175942555 / SKU 12000028287569580,https://aliexpress.ru/item/1005004175942555.html?sku_id=1200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,RelayStack:USB_C_Receptacle_HBXINTAO16PIN_DIP_Vertical,,,,,,,RelayStack:USB_C_Receptacle_HBXINTAO16PIN_DIP_Vertical
J3,DATA1–8 / 5V / GND,RelayStack:KF128-2.54-10P,1,,,,,,,RelayStack:KF128-2.54-10P,,,,,,,RelayStack:KF128-2.54-10P
J5,I²C,RelayStack:KF128-2.54-4P,1,,,,,,,RelayStack:KF128-2.54-4P,,,,,,,RelayStack:KF128-2.54-4P
J6,RIGHT · 12V / CTRL,RelayStack:StackHeader_2x03_P2.54mm_Bottom,1,,,,,,,RelayStack:StackHeader_2x03_P2.54mm_Bottom,,,,,,,RelayStack:StackHeader_2x03_P2.54mm_Bottom
J7,NET / PWR / STATUS / ALARM / GND,Connector_PinHeader_2.54mm:PinHeader_1x05_P2.54mm_Vertical,1,,,,,,,Connector_PinHeader_2.54mm:PinHeader_1x05_P2.54mm_Vertical,,,,,,,Connector_PinHeader_2.54mm:PinHeader_1x05_P2.54mm_Vertical
J8,RS-485 / 5V A B G,RelayStack:KF128-2.54-4P,1,,,,,,,RelayStack:KF128-2.54-4P,,,,,,,RelayStack:KF128-2.54-4P
J9,iButton LED / BUZZER / +12V,RelayStack:KF128-2.54-3P,1,,KF128-2.54-3P,Cixi Kefa,,,,RelayStack:KF128-2.54-3P,,,,,,,RelayStack:KF128-2.54-3P
JP2,TERM / normally open,Connector_PinHeader_2.54mm:PinHeader_1x02_P2.54mm_Vertical,1,,,,,,,Connector_PinHeader_2.54mm:PinHeader_1x02_P2.54mm_Vertical,,,,,,,Connector_PinHeader_2.54mm:PinHeader_1x02_P2.54mm_Vertical
"Q1, Q2, Q3",BC807-40,Package_TO_SOT_SMD:SOT-23,3,https://assets.nexperia.com/documents/data-sheet/BC807_SER.pdf,,,,,,Package_TO_SOT_SMD:SOT-23,,,,,,,Package_TO_SOT_SMD:SOT-23
"R1, R2, R51, R52, R73, R74",10k,Resistor_SMD:R_0805_2012Metric,6,,,,1%,,,0805,R-0805-10k-1pct-125mW,0.125 W,,,,,Resistor_SMD:R_0805_2012Metric
R3,1k,Resistor_SMD:R_0805_2012Metric,1,,,,,,,Resistor_SMD:R_0805_2012Metric,,,,,,,Resistor_SMD:R_0805_2012Metric
"R4, R23, R24, R25, R26, R46",470R,Resistor_SMD:R_0805_2012Metric,6,,,,1%,,,0805,R-0805-470R-1pct-125mW,0.125 W,,,,,Resistor_SMD:R_0805_2012Metric
"R5, R6, R7, R8, R11, R12, R47, R48, R49",22R,Resistor_SMD:R_0805_2012Metric,9,,,,1%,,,0805,R-0805-22R-1pct-125mW,0.125 W,,,,,Resistor_SMD:R_0805_2012Metric
"R9, R10",5.1k,Resistor_SMD:R_0805_2012Metric,2,,,,,,,Resistor_SMD:R_0805_2012Metric,,,,,,,Resistor_SMD:R_0805_2012Metric
R13,68k,Resistor_SMD:R_0805_2012Metric,1,,,,,,,Resistor_SMD:R_0805_2012Metric,,,,,,,Resistor_SMD:R_0805_2012Metric
"R14, R30, R31, R32",100k,Resistor_SMD:R_0805_2012Metric,4,,,,,,,Resistor_SMD:R_0805_2012Metric,,,,,,,Resistor_SMD:R_0805_2012Metric
"R15, R16, R19, R20, R33, R34, R37, R38, R57, R58",4.3k,Resistor_SMD:R_0805_2012Metric,10,,,,1%,,,Resistor_SMD:R_0805_2012Metric,,,,,,,Resistor_SMD:R_0805_2012Metric
"R17, R18, R21, R22, R27, R28, R29, R35, R36, R39, R40, R59, R60",4.7k,Resistor_SMD:R_0805_2012Metric,13,,,,1%,,,0805,R-0805-4.7k-1pct-125mW,0.125 W,,,,,Resistor_SMD:R_0805_2012Metric
"R50, R54, R55, R56",47k,Resistor_SMD:R_0805_2012Metric,4,,,,1%,,,Resistor_SMD:R_0805_2012Metric,,,,,,,Resistor_SMD:R_0805_2012Metric
R53,120R 0.25W,Resistor_SMD:R_1206_3216Metric,1,,,,1%,,,Resistor_SMD:R_1206_3216Metric,,,,,,,Resistor_SMD:R_1206_3216Metric
"R61, R62, R63, R64, R65, R66, R67, R68, R69, R70",100R,Resistor_SMD:R_0805_2012Metric,10,https://www.vishay.com/docs/20115/crcwhp.pdf,CRCW0805100RFKTAHP,Vishay,1%,,,Resistor_SMD:R_0805_2012Metric,,0.5 W,,,Pulse-withstanding,,Resistor_SMD:R_0805_2012Metric
"R71, R72",680R,Resistor_SMD:R_0805_2012Metric,2,,,,1%,,,0805,R-0805-680R-1pct-125mW,0.125 W,,,,,Resistor_SMD:R_0805_2012Metric
R75,1k / 0.5W,Resistor_SMD:R_0805_2012Metric,1,https://industrial.panasonic.com/cdbs/www-data/pdf/RDO0000/A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,ERJ-P06F1001V,Panasonic,1%,,,0805,R-0805-1k-1pct-500mW-Panasonic,0.5 W,,,,,Resistor_SMD:R_0805_2012Metric
SW1,RESET,RelayStack:SW_SPST_TS-1088-xR020,1,https://lcsc.com/datasheet/lcsc_datasheet_2504101957_XUNPU-T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,,,,,,RelayStack:SW_SPST_TS-1088-xR020,,,,,,,RelayStack:SW_SPST_TS-1088-xR020
SW2,BOOT,RelayStack:SW_SPST_TS-1088-xR020,1,https://lcsc.com/datasheet/lcsc_datasheet_2504101957_XUNPU-T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,,,,,,RelayStack:SW_SPST_TS-1088-xR020,,,,,,,RelayStack:SW_SPST_TS-1088-xR020
U1,ESP32-S3-WROOM-1U,RelayStack:ESP32-S3-WROOM-1U_PTH030,1,https://documentation.espressif.com/esp32-s3-wroom-1_wroom-1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,ESP32-S3-WROOM-1U-N16R8,Espressif Systems,,,,RelayStack:ESP32-S3-WROOM-1U_PTH030,,,,,,,RelayStack:ESP32-S3-WROOM-1U_PTH030
U2,W5500-Lite,RelayStack:W5500_Lite_2x6,1,https://www.pusr.com/download/ES1/USR-ES1_sch.pdf,,,,,,RelayStack:W5500_Lite_2x6,,,,,,,RelayStack:W5500_Lite_2x6
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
